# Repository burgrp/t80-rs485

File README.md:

# T80-RS485
T80 compatible RS485 interface

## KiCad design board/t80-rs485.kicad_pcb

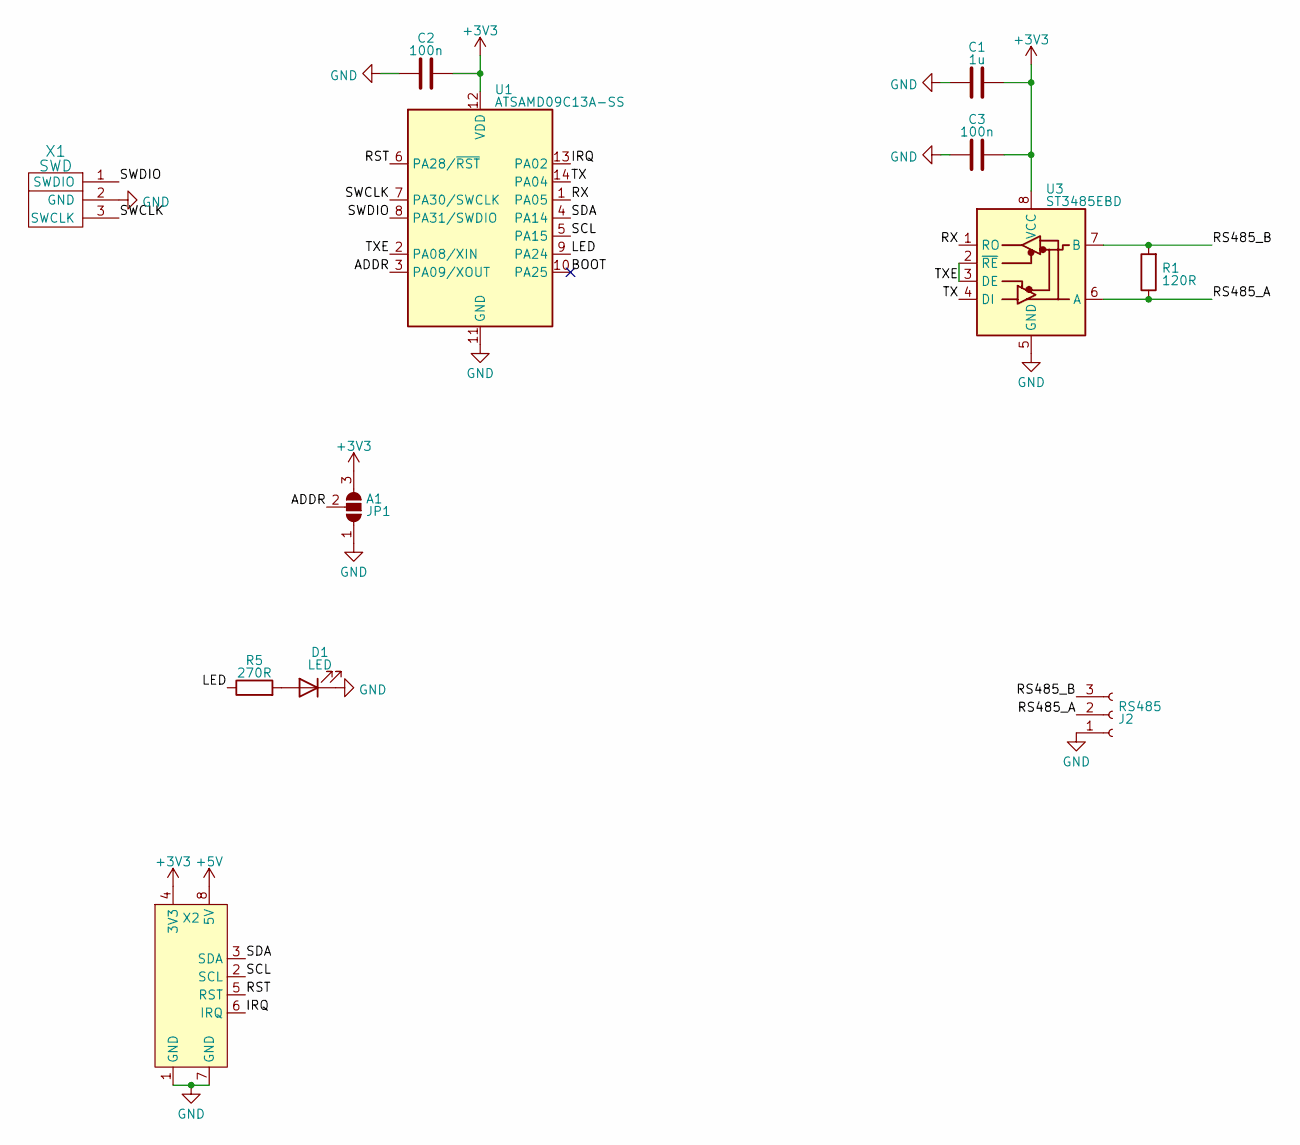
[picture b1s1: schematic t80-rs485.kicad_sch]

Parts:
C1: 1u; C_0805_2012Metric_Pad1.18x1.45mm_HandSolder
C2, C3: 100n; C_0805_2012Metric_Pad1.18x1.45mm_HandSolder
D1: LED; LED_0805_2012Metric_Pad1.15x1.40mm_HandSolder
J2: RS485; DG235-3.81-03P
JP1: A1; SolderJumper-3_P2.0mm_Open_TrianglePad1.0x1.5mm
R1: 120R; R_0805_2012Metric_Pad1.20x1.40mm_HandSolder
R5: 270R; R_0805_2012Metric_Pad1.20x1.40mm_HandSolder
U1: ATSAMD09C13A-SS; SOIC-14_3.9x8.7mm_P1.27mm
U3: ST3485EBD; SOIC-8_3.9x4.9mm_P1.27mm
X1: SWD
X2: IDC-Header_2x04_P2.54mm_Vertical

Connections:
+3V3: C1.2, C2.2, C3.2, JP1.3 (B), U1.12 (VDD), U3.8 (VCC), X2.4 (3V3)
+5V: X2.8 (5V)
/ADDR: JP1.2 (C), U1.3 (PA09/XOUT)
/BOOT: U1.10 (PA25)
/IRQ: U1.13 (PA02), X2.6 (IRQ)
/LED: R5.1, U1.9 (PA24)
/RS485_A: J2.2, R1.1, U3.6 (A)
/RS485_B: J2.3, R1.2, U3.7 (B)
/RST: U1.6 (PA28/~RST), X2.5 (RST)
/RX: U1.1 (PA05), U3.1 (RO)
/SCL: U1.5 (PA15), X2.2 (SCL)
/SDA: U1.4 (PA14), X2.3 (SDA)
/SWCLK: U1.7 (PA30/SWCLK), X1.3 (SWCLK)
/SWDIO: U1.8 (PA31/SWDIO), X1.1 (SWDIO)
/TX: U1.14 (PA04), U3.4 (DI)
/TXE: U1.2 (PA08/XIN), U3.2 (~RE), U3.3 (DE)
GND: C1.1, C2.1, C3.1, D1.1 (K), J2.1, JP1.1 (A), U1.11 (GND), U3.5 (GND), X1.2 (GND), X2.1 (GND), X2.7 (GND)
unnamed: D1.2 (A), R5.2

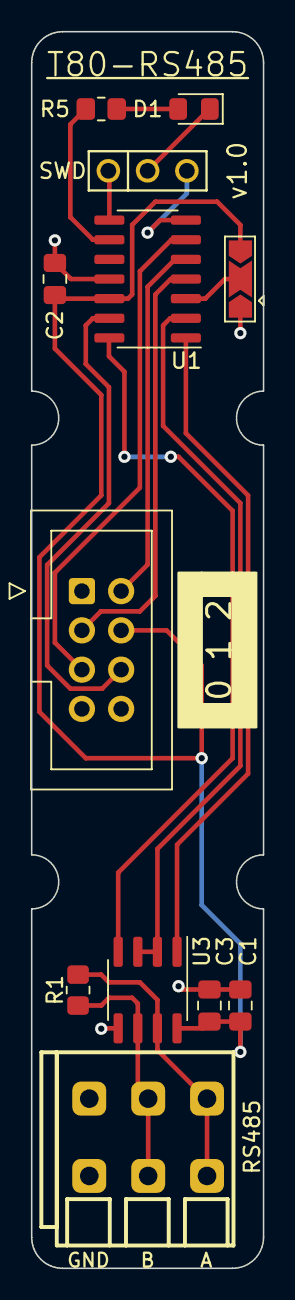
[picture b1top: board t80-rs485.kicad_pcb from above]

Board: 2 copper layers, 15.0 x 80.0 mm, 12 parts (0 on the bottom side), 16 nets.
